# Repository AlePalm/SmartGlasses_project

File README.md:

# AY2223_II_Project-3

GUI --> Folder containing the GUI, the images that are used within it and the model trained in the ML code
MACHINE LEARNING --> Folder containing the ML code and the dataset used to train the code
PCB --> Folder containing files to make the two PCBs mounted on the smart glasses
PRESENTATION --> Folder containing the Powerpoint presentation
PSOC --> Folder containing the c file to program the microcontroller, sensor communication and bluetooth communication with the computer
SAMPLE CODE --> Folder containing the python code used to acquire subjects and create the dataset used in the ML code

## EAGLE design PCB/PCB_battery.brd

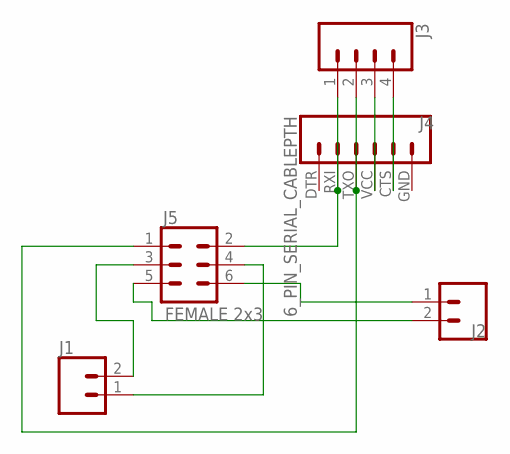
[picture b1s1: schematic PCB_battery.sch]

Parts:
J1, J2: CONN_02; 1X02
J3: CONN_04LOCK; 1X04_LOCK
J4: 6_PIN_SERIAL_CABLEPTH; FTDI_BASIC
J5: FEMALE 2x3; 2X3

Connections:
unnamed: J1.2, J5.3
unnamed: J1.1, J5.4
unnamed: J2.1, J5.6
unnamed: J2.2, J5.5
unnamed: J3.1, J4.RXI (2), J5.2
unnamed: J3.3, J4.VCC (4)
unnamed: J3.4, J4.CTS (5)
unnamed: J3.2, J4.TXO (3), J5.1

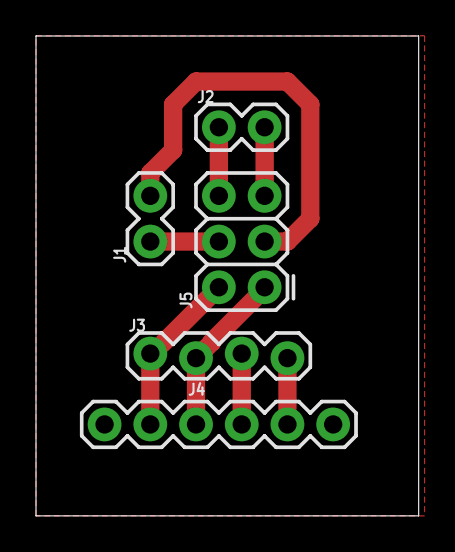
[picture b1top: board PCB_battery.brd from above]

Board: 2 copper layers, 21.3 x 26.7 mm, 5 parts (0 on the bottom side), 8 nets.

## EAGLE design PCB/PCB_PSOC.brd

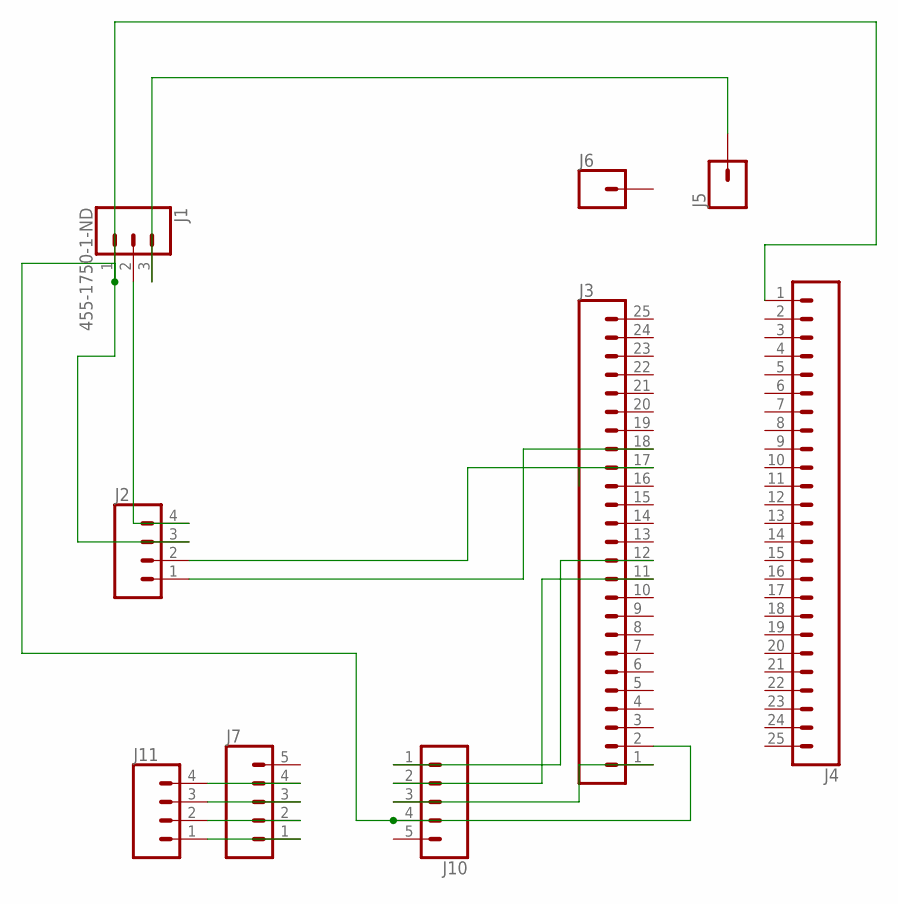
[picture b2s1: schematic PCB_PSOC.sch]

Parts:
J1: 455-1750-1-ND; 1X03
J2, J11: CONN_04PTH; 1X04
J3, J4: CONN_25; 1X25
J5, J6: CONN_01; 1X01
J7, J10: CONN_05; 1X05

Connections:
unnamed: J1.3, J5.1
unnamed: J2.1, J3.18
unnamed: J2.2, J3.17
unnamed: J3.12, J10.1
unnamed: J3.11, J10.2
unnamed: J3.1, J10.3
unnamed: J7.4, J11.4
unnamed: J1.2, J2.4
unnamed: J1.1, J2.3, J3.2, J4.1, J10.4
unnamed: J7.3, J11.3
unnamed: J7.2, J11.2
unnamed: J7.1, J11.1

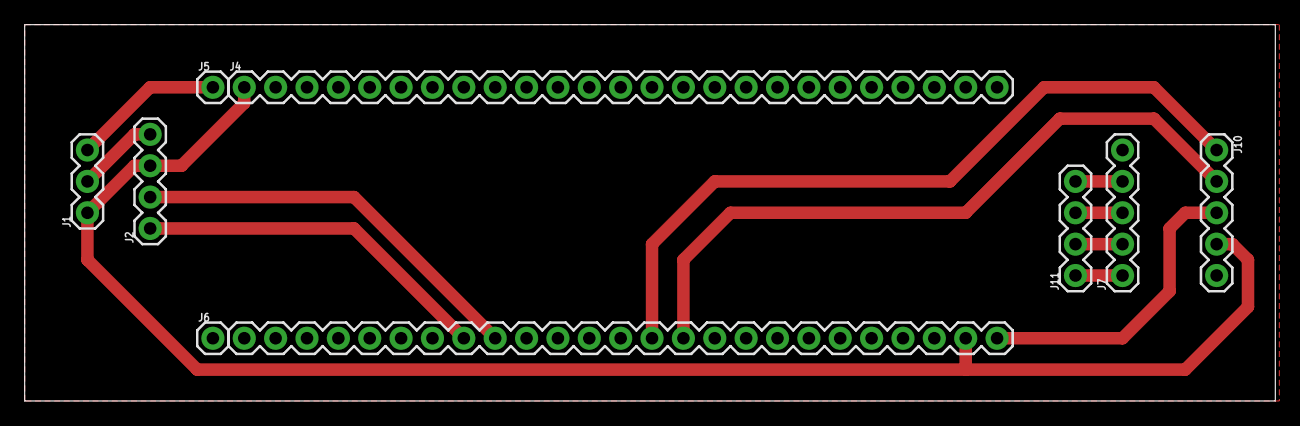
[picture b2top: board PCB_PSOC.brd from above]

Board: 2 copper layers, 101.3 x 30.5 mm, 9 parts (0 on the bottom side), 12 nets.

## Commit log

2024-09-03 add ReadMe file
2024-09-03 add gitignore
2024-09-03 adding all project files

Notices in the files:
parts and their libraries:
SparkFun-Connectors: Licensing: Creative Commons ShareAlike 4.0 International - https://creativecommons.org/licenses/by-sa/4.0
